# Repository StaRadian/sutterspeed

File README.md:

# sutterspeed

A light oscilloscope on a small USB board: a photodiode front end sampled at 400 kS/s, a Windows viewer
that works like a bench scope (time base, vertical scale, trigger, filters, measurements, cursors), and a
shutter measurement mode that times a single light pulse — the original purpose of the board was testing
camera shutter speeds.

## Hardware

- STM32C071G8 (Cortex-M0+, 48 MHz), USB full speed
- TEMD5510 photodiode, transimpedance stage (10 kΩ) followed by gains ×1 / ×11 / ×121
- the three stages are sampled together every 2.5 µs and merged into one wide-range value
  (the most sensitive stage that is not clipped; gain ratios are learned while running)

KiCad 10 project in [`kicad/`](kicad), fabrication files (BOM, positions, Gerbers) in [`kicad/production/`](kicad/production).

## Repository

| path | contents |
| --- | --- |
| [`firmware/src`](firmware/src) | firmware: ADC/DMA acquisition, scope engine (trigger, decimation, roll, pulse capture), USB CDC command line |
| [`firmware/tools/viewer-rs`](firmware/tools/viewer-rs) | Windows viewer (Rust, egui), also updates the firmware over USB |
| [`firmware/test`](firmware/test) | host test of the scope engine with synthetic light pulses |
| [`firmware/lib`](firmware/lib) | CMSIS, STM32C0 HAL, TinyUSB (git submodules) |
| [`code/`](code) | STM32CubeMX pin configuration |
| [`kicad/`](kicad) | schematic and PCB |

Clone with the libraries:

```
git clone --recursive https://github.com/StaRadian/sutterspeed.git
```

## Viewer

Download `sutterspeed-viewer.exe` from the [releases](https://github.com/StaRadian/sutterspeed/releases), plug in the
board and pick its COM port.

- **Horizontal**: 10 µs/div .. 5 s/div, position, sample rate (400 kS/s and divisions of it). Long time bases roll live.
- **Vertical**: lx/div and position, AUTO follows the signal smoothly; drag the trace to move it.
- **Trigger** (10 ms/div and faster; slower time bases roll live): AUTO / NORMAL / SINGLE, rising or falling edge,
  level knob or drag the ◀ marker. While SINGLE waits, the previous trace stays on screen, dimmed.
- **Filter**: moving average or low-pass on screen; the board triggers on the same filtered signal.
- **Min width** (next to the filter): light has to stay past the level at least this long to trigger, so short flashes
  and flicker are passed over. 0 = off (shown as HOLDOFF).
- **Measurements**: max, min, mean, peak-peak, flicker, frequency, period, width, duty, rise time; cursors A/B.
- **Shutter measurement** (pulse icon under the trigger, works like SINGLE): waits for one light pulse and shows it
  from start to end. The open time runs from the light rising through the trigger level to it falling back through it
  (on the filtered trace when a filter is set), with the nearest nominal speed and the error in EV. The trigger looks
  at a 40 µs average (or the filter), the timing at the 2.5 µs samples. Pulses from about 100 µs to tens of seconds.
  ▶ goes back to the running scope.
- **Update** (chip icon): *Update from GitHub* downloads the newest release, writes its firmware to the board when it
  is newer and replaces the viewer when it is newer (restart to use it). Firmware goes over USB through the board's
  own bootloader, which needs no driver; no STM32CubeProgrammer needed. Older boards (before 0.4.0) and blank chips
  are written through the ST bootloader; if the PC has no driver for it, the viewer installs Windows' own WinUSB
  (one Windows permission prompt). *Write built-in firmware* writes the firmware that comes inside the viewer
  (no internet needed, blank boards too); a `.hex`/`.bin` file can be written as well. From a script:
  `sutterspeed-viewer --flash [sutterspeed.hex]` (no file: the built-in one), `sutterspeed-viewer --update` (viewer only).

Build: the firmware first (`firmware/build/sutterspeed.hex` goes into the viewer), then
`cd firmware/tools/viewer-rs && cargo build --release`.

## Firmware

Build with [STM32CubeCLT](https://www.st.com/en/development-tools/stm32cubeclt.html) (arm-none-eabi-gcc, CMake, Ninja):

```
cd firmware
cmake -S . -B build -G Ninja
cmake --build build
```

See [`firmware/README.md`](firmware/README.md) for flashing and the serial protocol.

## Status and limits

- The lux scale comes from the datasheet (≈10 nA/lx for illuminant A, ≈15 counts per lx) and is not calibrated;
  other light sources (LED, daylight) can read tens of percent off. `zero` removes the dark offset only — cover the
  sensor when using it.
- The 2.5 µs samples are noisy (tens of lx at room light, and LED room light may flicker at tens of kHz);
  slower sample rates and the filters average it out. Set the shutter trigger level clearly above the room light.
- Measured on one board: stage ratios ×10.9 (×11 / ×1) and ×13.0 (×121 / ×11, nominal 11); the firmware learns
  them while running (`adc` and `gain` show them).

Copyright © 2026 StaRadian. All rights reserved. The libraries under `firmware/lib` keep their own licenses.

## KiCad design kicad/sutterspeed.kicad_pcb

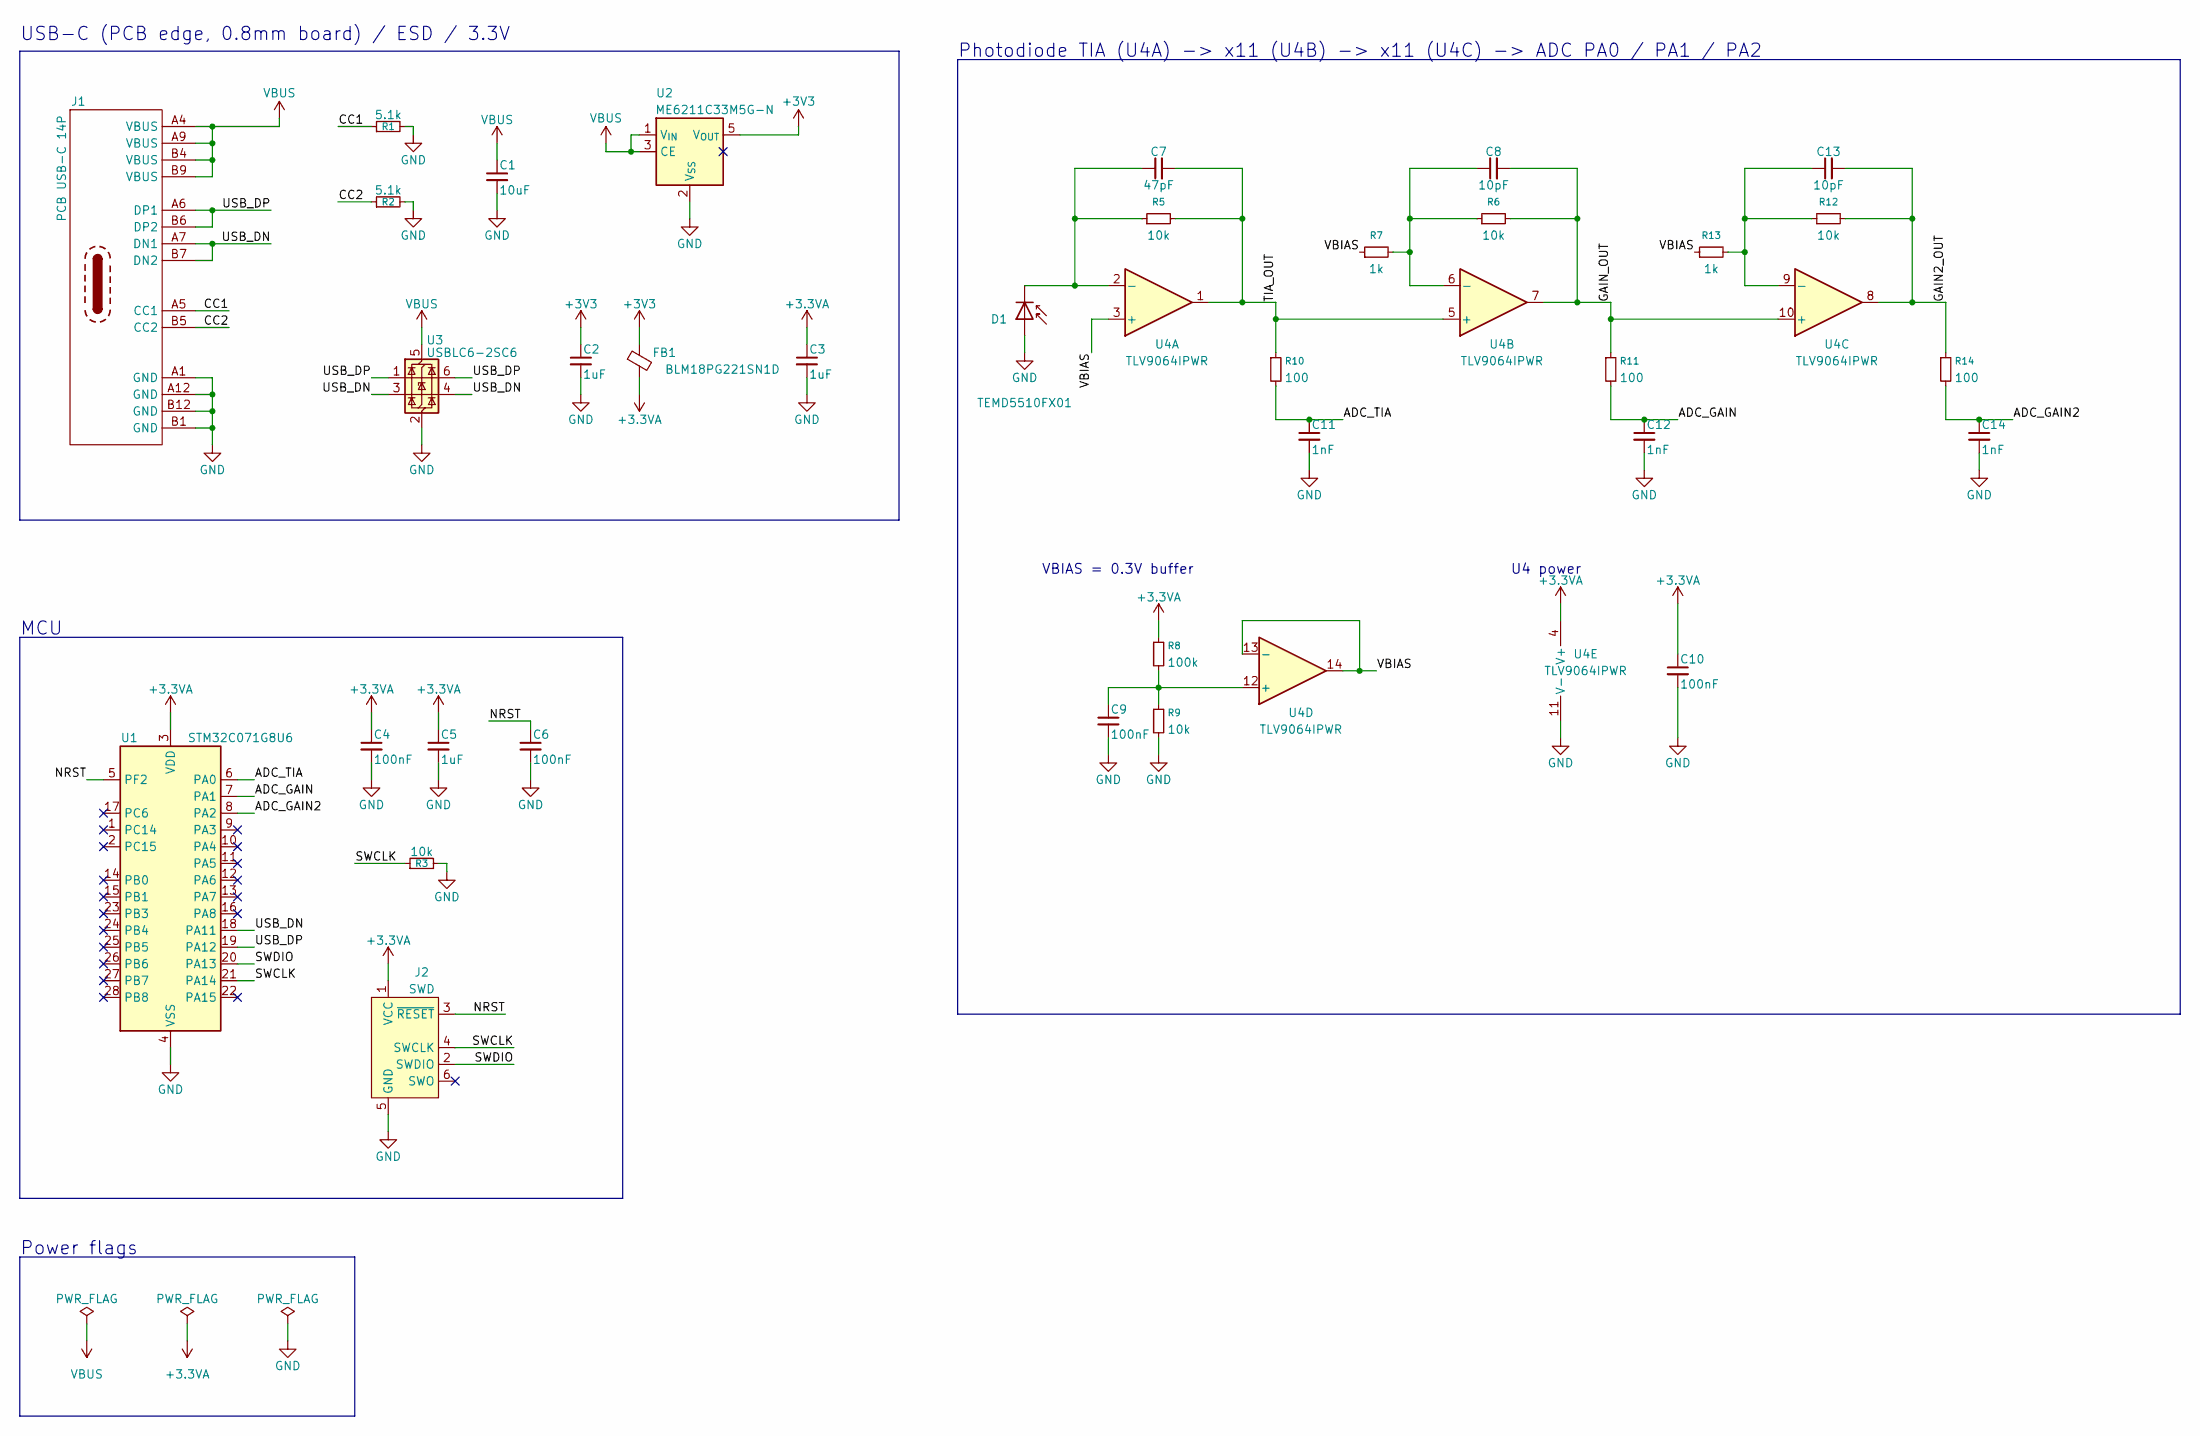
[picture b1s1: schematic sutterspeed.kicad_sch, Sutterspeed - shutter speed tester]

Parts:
C1: 10uF; C_0603_1608Metric; LCSC C19702
C2, C3, C5: 1uF; C_0402_1005Metric; LCSC C52923
C4, C6, C9, C10: 100nF; C_0402_1005Metric; LCSC C1525
C7: 47pF; C_0402_1005Metric; LCSC C1567
C8, C13: 10pF; C_0402_1005Metric; LCSC C32949
C11, C12, C14: 1nF; C_0402_1005Metric; LCSC C1523
D1: TEMD5510FX01; Vishay_TEMD5510FX01; MPN TEMD5510FX01; LCSC C94856
FB1: BLM18PG221SN1D; L_0603_1608Metric; LCSC C80165
J1: PCB USB-C 14P; PCBTypeC_14P
J2: SWD; Tag-Connect_TC2030-IDC-NL_2x03_P1.27mm_Vertical
R1, R2: 5.1k; R_0402_1005Metric; LCSC C25905
R3, R5, R6, R9, R12: 10k; R_0402_1005Metric; LCSC C25744
R7, R13: 1k; R_0402_1005Metric; LCSC C11702
R8: 100k; R_0402_1005Metric; LCSC C25741
R10, R11, R14: 100; R_0402_1005Metric; LCSC C25076
U1: STM32C071G8U6; QFN-28_4x4mm_P0.5mm; LCSC C44521811
U2: ME6211C33M5G-N; SOT-23-5; LCSC C82942
U3: USBLC6-2SC6; SOT-23-6; LCSC C7519
U4: TLV9064IPWR; TSSOP-14_4.4x5mm_P0.65mm; LCSC C779410

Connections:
+3.3VA: C3.1, C4.1, C5.1, C10.1, FB1.2, J2.1 (VCC), R8.1, U1.3 (VDD), U4.4 (V+)
+3V3: C2.1, FB1.1, U2.5 (V_{OUT})
/ADC_GAIN: C12.1, R11.2, U1.7 (PA1)
/ADC_GAIN2: C14.1, R14.2, U1.8 (PA2)
/ADC_TIA: C11.1, R10.2, U1.6 (PA0)
/CC1: J1.A5 (CC1), R1.1
/CC2: J1.B5 (CC2), R2.1
/GAIN2_OUT: C13.2, R12.2, R14.1, U4.8
/GAIN_OUT: C8.2, R6.2, R11.1, U4.7, U4.10 (+)
/NRST: C6.1, J2.3 (~RESET), U1.5 (PF2)
/SWCLK: J2.4 (SWCLK), R3.1, U1.21 (PA14)
/SWDIO: J2.2 (SWDIO), U1.20 (PA13)
/TIA_OUT: C7.2, R5.2, R10.1, U4.1, U4.5 (+)
/USB_DN: J1.A7 (DN1), J1.B7 (DN2), U1.18 (PA11), U3.3 (I/O2), U3.4 (I/O2)
/USB_DP: J1.A6 (DP1), J1.B6 (DP2), U1.19 (PA12), U3.1 (I/O1), U3.6 (I/O1)
/VBIAS: R7.1, R13.1, U4.3 (+), U4.13 (-), U4.14
GND: C1.2, C2.2, C3.2, C4.2, C5.2, C6.2, C9.2, C10.2, C11.2, C12.2, C14.2, D1.2 (A), J1.A1 (GND), J1.A12 (GND), J1.B1 (GND), J1.B12 (GND), J2.5 (GND), R1.2, R2.2, R3.2, R9.2, U1.4 (VSS), U2.2 (V_{SS}), U3.2 (GND), U4.11 (V-)
unnamed: C7.1, D1.1 (K), R5.1, U4.2 (-)
unnamed: C8.1, R6.1, R7.2, U4.6 (-)
unnamed: C13.1, R12.1, R13.2, U4.9 (-)
unnamed: C9.1, R8.2, R9.1, U4.12 (+)
VBUS: C1.1, J1.A4 (VBUS), J1.A9 (VBUS), J1.B4 (VBUS), J1.B9 (VBUS), U2.1 (V_{IN}), U2.3 (CE), U3.5 (VBUS)

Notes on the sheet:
Photodiode TIA (U4A) -> x11 (U4B) -> x11 (U4C) -> ADC PA0 / PA1 / PA2
USB-C (PCB edge, 0.8mm board) / ESD / 3.3V
Power flags
MCU
VBIAS = 0.3V buffer
U4 power

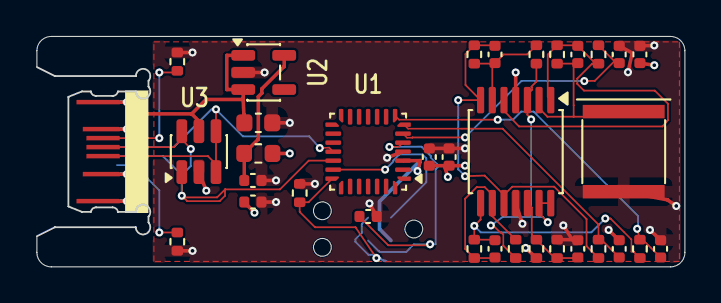
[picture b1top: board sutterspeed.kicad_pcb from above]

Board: 4 copper layers, 36.0 x 12.8 mm, 35 parts (1 on the bottom side), 22 nets.

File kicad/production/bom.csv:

Designator,Footprint,Quantity,Value,LCSC Part #
C1,0603,1,10uF,C19702
"C10, C4, C6, C9",0402,4,100nF,C1525
"C11, C12, C14",0402,3,1nF,C1523
"C13, C8",0402,2,10pF,C32949
"C2, C3, C5",0402,3,1uF,C52923
C7,0402,1,47pF,C1567
D1,Vishay_TEMD5510FX01,1,TEMD5510FX01,C94856
FB1,0603,1,BLM18PG221SN1D,C80165
"R1, R2",0402,2,5.1k,C25905
"R10, R11, R14",0402,3,100,C25076
"R12, R3, R5, R6, R9",0402,5,10k,C25744
"R13, R7",0402,2,1k,C11702
R8,0402,1,100k,C25741
U1,QFN-28_4x4mm_P0.5mm,1,STM32C071G8U6,C44521811
U2,SOT-23-5,1,ME6211C33M5G-N,C82942
U3,SOT-23-6,1,USBLC6-2SC6,C7519
U4,TSSOP-14_4.4x5mm_P0.65mm,1,TLV9064IPWR,C779410

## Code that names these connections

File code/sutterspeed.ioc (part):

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Mcu.Name=STM32C071G8Ux
Mcu.Package=UFQFPN28_GP
Mcu.UserName=STM32C071G8Ux
PA0.Mode=IN0
PA0.Signal=ADC1_IN0
PA11\ [PA9].Mode=Device
PA11\ [PA9].Signal=USB_DM
PA12\ [PA10].Mode=Device
PA12\ [PA10].Signal=USB_DP
PA13.Mode=Serial_Wire
PA13.Signal=DEBUG_SWDIO
PA14-BOOT0.Mode=Serial_Wire
PA14-BOOT0.Signal=DEBUG_SWCLK
PC14-OSCX_IN(PC14).Mode=HSE-External-Clock-Source
PC14-OSCX_IN(PC14).Signal=RCC_OSCX_IN
RCC.HSE_VALUE=8000000
RCC.SYSCLKFreq_VALUE=12000000
board=custom
